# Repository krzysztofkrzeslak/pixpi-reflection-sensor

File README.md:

# pixpi-sound-sensor
Repository which holds reflection sensor sources(schematic and board)for PiXPi controller <br/>

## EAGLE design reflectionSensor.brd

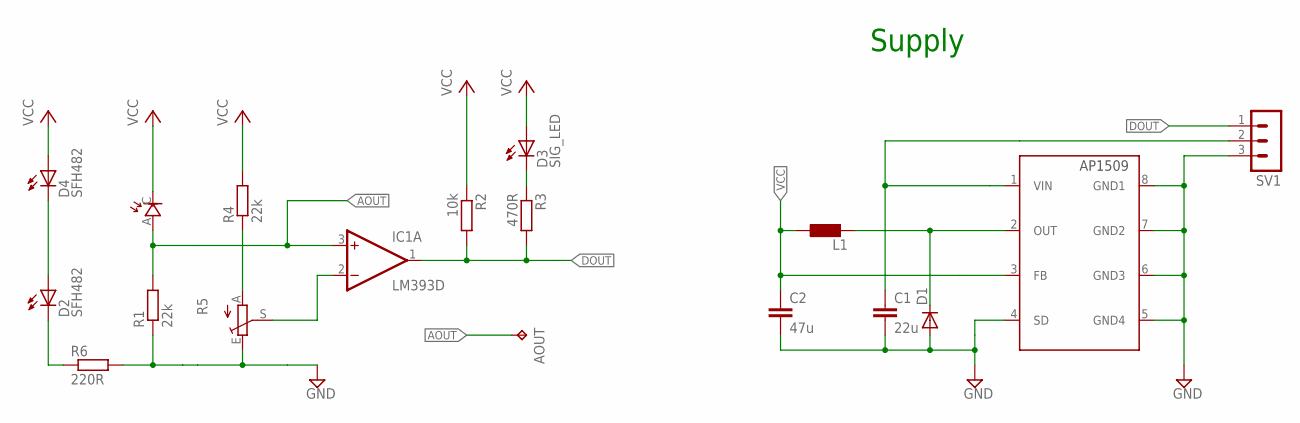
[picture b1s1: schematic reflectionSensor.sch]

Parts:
AOUT: TPTP20SQ; TP20SQ
C1: 22u; C1210
C2: 47u; C1210
D1: DIODE-SOD323-W; SOD323-W
D2, D4: SFH482
D3: SIG_LED; SFH482
IC1: LM393D; SO08
L1: LL5650M; L5650M
R1, R4: 22k; M1206
R2: 10k; M0805
R3: 470R; M0805
R5: TRIM_EU-CA9V; CA9V
R6: 220R; M1206
SV1: MA03-1
U$1: AP1509; SOP08
U$2: PHOTODIODE

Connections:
AOUT: AOUT.TP, IC1.3 (+IN), R1.2, U$2.A
DOUT: IC1.1 (OUT), R2.2, R3.2, SV1.1
GND: C1.2, C2.2, D1.A, IC1.4 (V-), R1.1, R5.E, R6.2, SV1.3, U$1.4 (SD), U$1.5 (GND4), U$1.6 (GND3), U$1.7 (GND2), U$1.8 (GND1)
unnamed: D2.A, D4.K (C)
unnamed: C1.1, SV1.2, U$1.1 (VIN)
unnamed: D1.C, L1.2, U$1.2 (OUT)
unnamed: D3.K (C), R3.1
unnamed: IC1.2 (-IN), R5.S
unnamed: R4.1, R5.A
unnamed: D2.K (C), R6.1
VCC: C2.1, D3.A, D4.A, IC1.8 (V+), L1.1, R2.1, R4.2, U$1.3 (FB), U$2.C

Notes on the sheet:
Supply

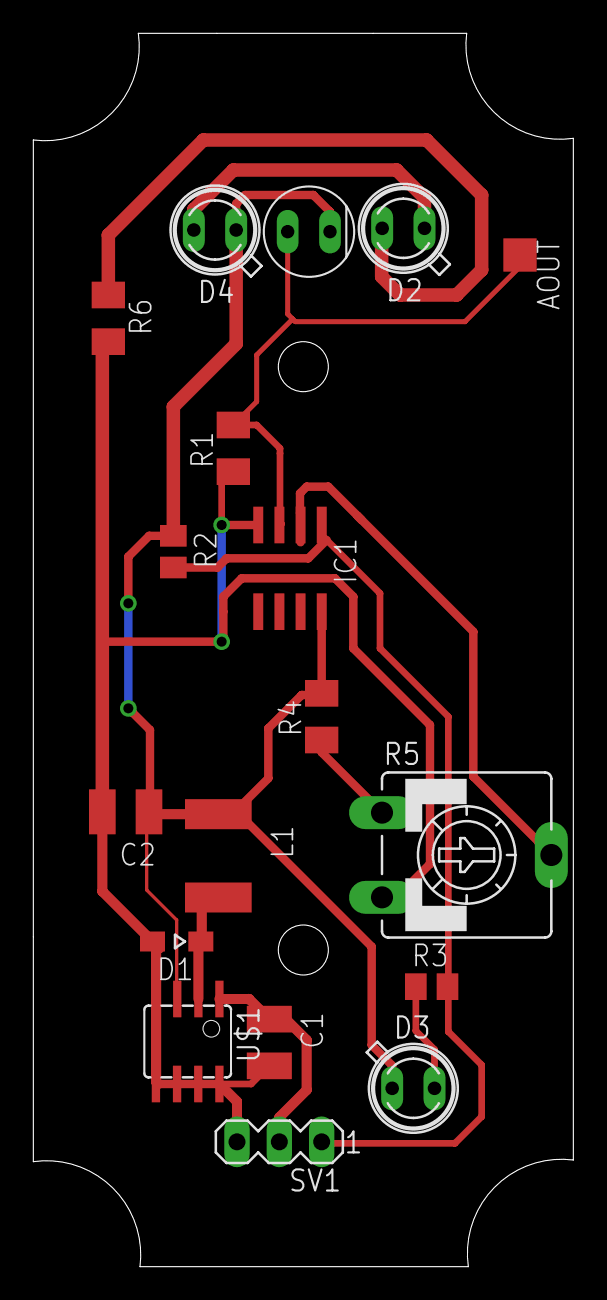
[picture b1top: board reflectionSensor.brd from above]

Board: 2 copper layers, 32.4 x 74.0 mm, 18 parts (0 on the bottom side), 11 nets.

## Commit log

2019-08-23 Added schematic, board and readme
